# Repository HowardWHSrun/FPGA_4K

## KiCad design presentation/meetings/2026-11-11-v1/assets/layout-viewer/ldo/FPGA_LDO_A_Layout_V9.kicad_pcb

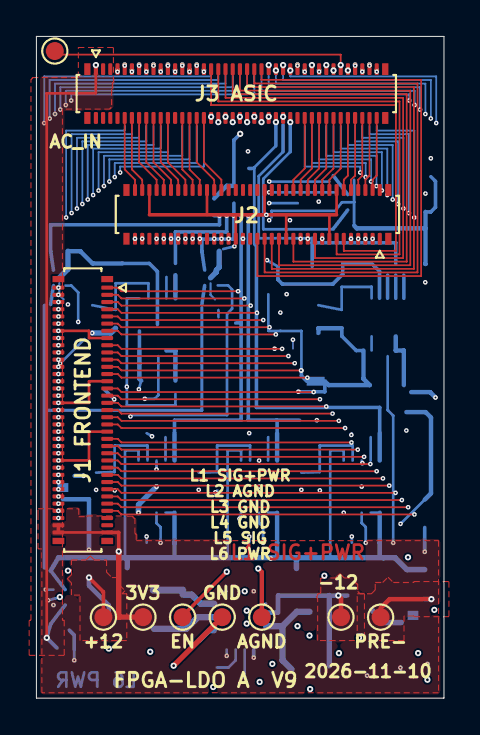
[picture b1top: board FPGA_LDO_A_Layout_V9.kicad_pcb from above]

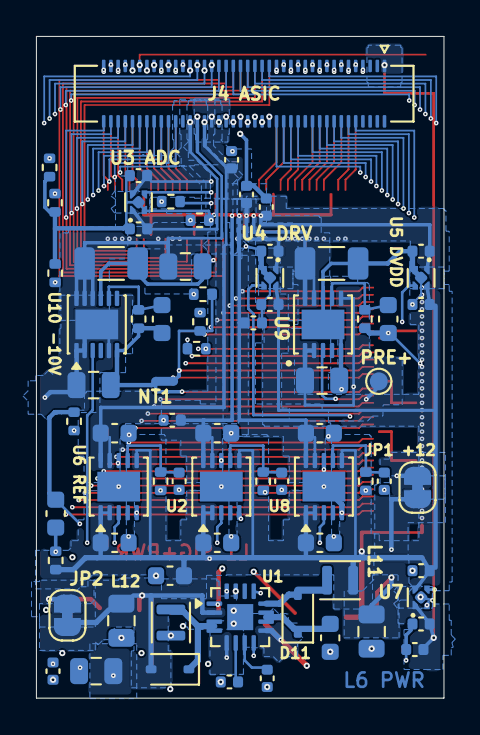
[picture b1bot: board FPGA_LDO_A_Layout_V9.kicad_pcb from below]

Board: 6 copper layers, 22.6 x 36.8 mm, 84 parts (73 on the bottom side), 136 nets.

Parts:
C1, C14, C21: 22uF; C_0805_2012Metric
C2: 100nF; C_0402_1005Metric
C3, C11: 4.7uF; C_0603_1608Metric
C15, C903, C1003: 1uF; C_0603_1608Metric
C16, C17: 10nF; C_0402_1005Metric
C51, C53, C54, C55, C56, C57, C203, C301, C302, C401, C402, C501, C502, C603, C701, C702, C803: 1uF; C_0402_1005Metric
C201, C202, C601, C602, C801, C802: 10uF; C_0603_1608Metric
C901, C1001, C1004: 10uF; C_0805_2012Metric
C902, C1002: 22uF; C_1206_3216Metric
D11, D12: B0540WS-7; D_SOD-323
J1, J2: DF40C-70DP-0.4V(51); Hirose_DF40C-70DP-0.4V_2x35-1MP_P0.4mm
J3: DF40C-80DP-0.4V(51); Hirose_DF40C-80DP-0.4V_2x40-1MP_P0.4mm
J4: DF40C-80DS-0.4V(51); Hirose_DF40C-80DS-0.4V_2x40_P0.4mm
JP1, JP2: Bridged; SolderJumper-2_P1.3mm_Bridged_RoundedPad1.0x1.5mm
L11, L12: 6.8uH; L_Murata_DFE201610P
NT1: NetTie_2; NetTie-2_SMD_Pad0.5mm
R1, R2, R3, R4, R5, R6, R16, R17, R18, R19: 10k; R_0402_1005Metric
R201, R601: 15k; R_0402_1005Metric
R801: 7.5k; R_0402_1005Metric
R901, R1001: 100k; R_0402_1005Metric
TP1: VIN_3V3; TestPoint_Pad_D1.0mm_Compact
TP2: STIM_POS_12V; TestPoint_Pad_D1.0mm_Compact
TP3: STIM_NEG_12V; TestPoint_Pad_D1.0mm_Compact
TP4: EN_ASIC_RAILS; TestPoint_Pad_D1.0mm_Compact
TP5: GND; TestPoint_Pad_D1.0mm_Compact
TP6: AGND; TestPoint_Pad_D1.0mm_Compact
TP7: ASIC_AC_IN; TestPoint_Pad_D1.0mm_Compact
TP8: STIM_PRE_POS; TestPoint_Pad_D1.0mm_Compact
TP9: STIM_PRE_NEG; TestPoint_Pad_D1.0mm_Compact
U1: LT3582EUD-12#PBF; QFN-16-1EP_3x3mm_P0.5mm_EP1.45x1.45mm
U2, U6, U8, U9: LT3042EDD#PBF; DFN-10-1EP_3x3mm_P0.5mm_EP1.65x2.38mm
U3, U4, U5, U7: TPS7A2015PDQNR; Texas_X2SON-4_1x1mm_P0.65mm
U10: LT3094EDD#PBF; DFN-12-1EP_3x3mm_P0.45mm_EP1.65x2.38mm

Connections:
/ASIC1_CLK32MHz_Out: J1.53, J4.45
/ASIC1_DATA1: J1.25, J4.79
/ASIC1_DATA2: J1.23, J4.77
/ASIC1_DATA3: J1.21, J4.75
/ASIC1_DATA4: J1.19, J4.73
/ASIC1_DATA5: J1.12, J4.43
/ASIC1_DATA6: J1.10, J4.41
/ASIC1_DATA7: J1.8, J4.39
/ASIC1_DATA8: J1.6, J4.37
/ASIC1_READ: J1.4, J4.35
/ASIC1_SYNC: J1.55, J4.47
/ASIC2_CLK32MHz_Out: J1.54, J4.19
/ASIC2_DATA1: J1.2, J4.33
/ASIC2_DATA2: J1.1, J4.31
/ASIC2_DATA3: J1.64, J4.29
/ASIC2_DATA4: J1.62, J4.27
/ASIC2_DATA5: J1.52, J4.17
/ASIC2_DATA6: J1.48, J4.15
/ASIC2_DATA7: J1.46, J4.13
/ASIC2_DATA8: J1.44, J4.11
/ASIC2_READ: J1.42, J4.9
/ASIC2_SYNC: J1.56, J4.21
/ASIC3_CLK32MHz_Out: J1.39, J4.70
/ASIC3_DATA1: J1.51, J4.80
/ASIC3_DATA2: J1.49, J4.78
/ASIC3_DATA3: J1.47, J4.76
/ASIC3_DATA4: J1.45, J4.74
/ASIC3_DATA5: J1.37, J4.68
/ASIC3_DATA6: J1.35, J4.66
/ASIC3_DATA7: J1.33, J4.64
/ASIC3_DATA8: J1.31, J4.62
/ASIC3_READ: J1.29, J4.60
/ASIC3_SYNC: J1.43, J4.72
/ASIC4_CLK32MHz_Out: J1.26, J4.20
/ASIC4_DATA1: J1.38, J4.32
/ASIC4_DATA2: J1.36, J4.30
/ASIC4_DATA3: J1.32, J4.28
/ASIC4_DATA4: J1.30, J4.26
/ASIC4_DATA5: J1.24, J4.18
/ASIC4_DATA6: J1.22, J4.16
/ASIC4_DATA7: J1.20, J4.14
/ASIC4_DATA8: J1.18, J4.12
/ASIC4_READ: J1.16, J4.10
/ASIC4_SYNC: J1.28, J4.22
/ASIC5_CLK32MHz_Out: J2.33, J3.45
/ASIC5_DATA1: J2.3, J3.79
/ASIC5_DATA2: J2.5, J3.77
/ASIC5_DATA3: J2.7, J3.75
/ASIC5_DATA4: J2.9, J3.73
/ASIC5_DATA5: J2.31, J3.43
/ASIC5_DATA6: J2.29, J3.41
/ASIC5_DATA7: J2.25, J3.39
/ASIC5_DATA8: J2.19, J3.37
/ASIC5_READ: J2.13, J3.35
/ASIC5_SYNC: J2.35, J3.47
/ASIC6_CLK32MHz_Out: J2.55, J3.19
/ASIC6_DATA1: J2.11, J3.33
/ASIC6_DATA2: J2.39, J3.31
/ASIC6_DATA3: J2.43, J3.29
/ASIC6_DATA4: J2.45, J3.27
/ASIC6_DATA5: J2.57, J3.17
/ASIC6_DATA6: J2.59, J3.15
/ASIC6_DATA7: J2.61, J3.13
/ASIC6_DATA8: J2.63, J3.11
/ASIC6_READ: J2.67, J3.9
/ASIC6_SYNC: J2.53, J3.21
/ASIC7_CLK32MHz_Out: J2.16, J3.70
/ASIC7_DATA1: J2.4, J3.80
/ASIC7_DATA2: J2.6, J3.78
/ASIC7_DATA3: J2.8, J3.76
/ASIC7_DATA4: J2.10, J3.74
/ASIC7_DATA5: J2.18, J3.68
/ASIC7_DATA6: J2.20, J3.66
/ASIC7_DATA7: J2.22, J3.64
/ASIC7_DATA8: J2.24, J3.62
/ASIC7_READ: J2.26, J3.60
/ASIC7_SYNC: J2.12, J3.72
/ASIC8_CLK32MHz_Out: J2.58, J3.20
/ASIC8_DATA1: J2.46, J3.32
/ASIC8_DATA2: J2.48, J3.30
/ASIC8_DATA3: J2.52, J3.28
/ASIC8_DATA4: J2.54, J3.26
/ASIC8_DATA5: J2.60, J3.18
/ASIC8_DATA6: J2.62, J3.16
/ASIC8_DATA7: J2.64, J3.14
/ASIC8_DATA8: J2.68, J3.12
/ASIC8_READ: J2.70, J3.10
/ASIC8_SYNC: J2.56, J3.22
/ASIC_AC_IN: J3.69, J4.69, R6.1, TP7.1
/ASIC_DVDD: C54.1, C502.1, J3.34, J4.34, R19.2, U5.1
/ASIC_REF_VCM: C57.1, C802.1, J3.40, J4.40, U8.9, U8.10
/ASIC_REF_VDD: C55.1, C602.1, J3.52, J4.52, U6.9, U6.10
/ASIC_VDD10: C902.1, J3.36, J4.36, U9.9, U9.10
/ASIC_VDD_ADC: C302.1, J3.56, J4.56, U3.1
/ASIC_VDD_CGEN: C56.1, C702.1, J3.1, J4.1, U7.1
/ASIC_VDD_DRIVER: C53.1, C402.1, J3.38, J4.38, U4.1
/ASIC_VDD_FE: C51.1, C202.1, J3.50, J4.50, U2.9, U2.10
/ASIC_VSS10: C1002.1, C1004.1, J3.54, J4.54, U10.10, U10.11, U10.12
/BOARD1_CLK: J1.40, J4.7
/BOARD1_SPI_CLK: J1.9, J4.63
/BOARD3_CLK: J2.69, J3.7
/BOARD3_SPI_CLK: J2.17, J3.63
/CAPP: C15.1, D11.1, U1.10, U1.11
/CHIP_RESET_SHARED: J1.17, J3.71, J4.71, R19.1
/EN_ASIC_RAILS: C3.1, R1.2, TP4.1, U1.8, U2.3, U3.3, U4.3, U5.3, U6.3, U7.3, U8.3, U9.3, U10.3
/FE_RESET_SHARED: J1.11, J3.65, J4.65, R16.1
/IMP_TST_SHARED: J1.13, J3.67, J4.67, R17.1
/RAMPN: C17.1, U1.6
/RAMPP: C16.1, U1.7
/SPI_LATCH_SHARED: J1.7, J3.61, J4.61, R18.1
/STIM_CHB_SHARED: J1.57, J3.49, J4.49, R4.1
/STIM_CHIP1_SPI_DL: J1.5, J4.59
/STIM_CHIP1_SPI_DR: J1.3, J4.57
/STIM_CHIP2_SPI_DL: J1.60, J4.25
/STIM_CHIP2_SPI_DR: J1.58, J4.23
/STIM_CHIP3_SPI_DL: J2.21, J3.59
/STIM_CHIP3_SPI_DR: J2.23, J3.57
/STIM_CHIP4_SPI_DL: J2.47, J3.25
/STIM_CHIP4_SPI_DR: J2.51, J3.23
/STIM_CLK_SHARED: J1.61, J3.53, J4.53, R5.1
/STIM_EN_SHARED: J1.59, J3.51, J4.51, R2.1
/STIM_NEG_12V: C21.1, D12.2, JP2.1, TP3.1, U1.2
/STIM_POS_12V: C14.1, JP1.1, TP2.1, U1.9
/STIM_PRE_NEG: C1001.1, JP2.2, TP9.1, U10.1, U10.2, U10.5, U10.13
/STIM_PRE_POS: C901.1, JP1.2, TP8.1, U9.1, U9.2, U9.6
/STIM_START_SHARED: J1.63, J3.55, J4.55, R3.1
/SW_N: D12.1, L12.1, U1.3, U1.4
/SW_P: D11.2, L11.2, U1.12
/VIN_3V3: C1.1, C2.1, C11.1, C201.1, C301.1, C401.1, C501.1, C601.1, C701.1, C801.1, J1.68, J1.69, J1.70, L11.1, R1.1, TP1.1, U1.5, U2.1, U2.2, U2.6, U3.4, U4.4, U5.4, U6.1, U6.2, U6.6, U7.4, U8.1, U8.2, U8.6
AGND: C51.2, C53.2, C54.2, C55.2, C56.2, C57.2, C201.2, C202.2, C203.2, C401.2, C402.2, C501.2, C502.2, C601.2, C602.2, C603.2, C701.2, C702.2, C801.2, C802.2, C803.2, C901.2, C902.2, C903.2, C1001.2, C1002.2, C1003.2, C1004.2, J3.42, J3.44, J4.42, J4.44, NT1.2, R6.2, R201.2, R601.2, R801.2, R901.2, R1001.2, TP6.1, U2.5, U2.8, U2.11, U4.2, U4.5, U5.2, U5.5, U6.5, U6.8, U6.11, U7.2, U7.5, U8.5, U8.8, U8.11, U9.5, U9.8, U9.11, U10.6, U10.9
GND: C1.2, C2.2, C3.2, C11.2, C14.2, C15.2, C16.2, C17.2, C21.2, C301.2, C302.2, J1.14, J1.15, J1.27, J1.34, J1.41, J1.50, J1.66, J2.14, J2.15, J2.27, J2.34, J2.41, J2.50, J2.66, J3.46, J3.48, J4.46, J4.48, L12.2, NT1.1, R2.2, R3.2, R4.2, R5.2, R16.2, R17.2, R18.2, TP5.1, U1.1, U1.13, U1.15, U1.16, U1.17, U3.2, U3.5
unnamed: C203.1, R201.1, U2.7
unnamed: C603.1, R601.1, U6.7
unnamed: C803.1, R801.1, U8.7
unnamed: C903.1, R901.1, U9.7
unnamed: C1003.1, R1001.1, U10.8

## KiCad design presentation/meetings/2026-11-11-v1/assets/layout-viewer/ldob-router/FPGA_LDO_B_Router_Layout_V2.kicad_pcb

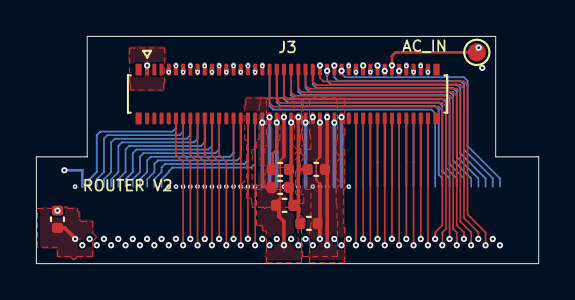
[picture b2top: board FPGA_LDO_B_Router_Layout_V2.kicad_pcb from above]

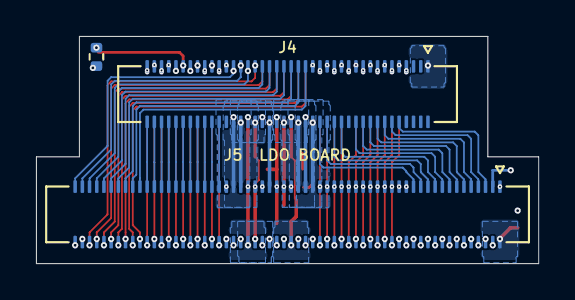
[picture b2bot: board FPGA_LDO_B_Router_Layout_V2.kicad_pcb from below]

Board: 6 copper layers, 27.9 x 12.6 mm, 11 parts (3 on the bottom side), 120 nets.

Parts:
C51, C53, C54, C55, C56, C57: 1uF; C_0402_1005Metric
J3: DF40C-80DP-0.4V(51); Hirose_DF40C-80DP-0.4V_2x40-1MP_P0.4mm
J4: DF40C-80DS-0.4V(51); Hirose_DF40C-80DS-0.4V_2x40_P0.4mm
J5: DF40C-120DS-0.4V(51); Hirose_DF40C-120DS-0.4V_2x60_P0.4mm
R6: 10k; R_0402_1005Metric
TP7: ASIC_AC_IN; TestPoint_Pad_D1.0mm_Compact

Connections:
/ASIC1_CLK32MHz_Out: J4.45, J5.111
/ASIC1_DATA1: J4.79, J5.77
/ASIC1_DATA2: J4.77, J5.76
/ASIC1_DATA3: J4.75, J5.74
/ASIC1_DATA4: J4.73, J5.71
/ASIC1_DATA5: J4.43, J5.109
/ASIC1_DATA6: J4.41, J5.107
/ASIC1_DATA7: J4.39, J5.105
/ASIC1_DATA8: J4.37, J5.103
/ASIC1_READ: J4.35, J5.101
/ASIC1_SYNC: J4.47, J5.113
/ASIC2_CLK32MHz_Out: J4.19, J5.39
/ASIC2_DATA1: J4.33, J5.1
/ASIC2_DATA2: J4.31, J5.51
/ASIC2_DATA3: J4.29, J5.49
/ASIC2_DATA4: J4.27, J5.47
/ASIC2_DATA5: J4.17, J5.37
/ASIC2_DATA6: J4.15, J5.35
/ASIC2_DATA7: J4.13, J5.33
/ASIC2_DATA8: J4.11, J5.31
/ASIC2_READ: J4.9, J5.29
/ASIC2_SYNC: J4.21, J5.41
/ASIC3_CLK32MHz_Out: J4.70, J5.89
/ASIC3_DATA1: J4.80, J5.99
/ASIC3_DATA2: J4.78, J5.97
/ASIC3_DATA3: J4.76, J5.95
/ASIC3_DATA4: J4.74, J5.93
/ASIC3_DATA5: J4.68, J5.87
/ASIC3_DATA6: J4.66, J5.85
/ASIC3_DATA7: J4.64, J5.83
/ASIC3_DATA8: J4.62, J5.81
/ASIC3_READ: J4.60, J5.79
/ASIC3_SYNC: J4.72, J5.91
/ASIC4_CLK32MHz_Out: J4.20, J5.15
/ASIC4_DATA1: J4.32, J5.25
/ASIC4_DATA2: J4.30, J5.23
/ASIC4_DATA3: J4.28, J5.21
/ASIC4_DATA4: J4.26, J5.19
/ASIC4_DATA5: J4.18, J5.13
/ASIC4_DATA6: J4.16, J5.11
/ASIC4_DATA7: J4.14, J5.9
/ASIC4_DATA8: J4.12, J5.7
/ASIC4_READ: J4.10, J5.5
/ASIC4_SYNC: J4.22, J5.17
/ASIC5_CLK32MHz_Out: J3.45, J5.112
/ASIC5_DATA1: J3.79, J5.120
/ASIC5_DATA2: J3.77, J5.118
/ASIC5_DATA3: J3.75, J5.78
/ASIC5_DATA4: J3.73, J5.68
/ASIC5_DATA5: J3.43, J5.110
/ASIC5_DATA6: J3.41, J5.108
/ASIC5_DATA7: J3.39, J5.106
/ASIC5_DATA8: J3.37, J5.104
/ASIC5_READ: J3.35, J5.102
/ASIC5_SYNC: J3.47, J5.114
/ASIC6_CLK32MHz_Out: J3.19, J5.16
/ASIC6_DATA1: J3.33, J5.30
/ASIC6_DATA2: J3.31, J5.28
/ASIC6_DATA3: J3.29, J5.26
/ASIC6_DATA4: J3.27, J5.24
/ASIC6_DATA5: J3.17, J5.14
/ASIC6_DATA6: J3.15, J5.12
/ASIC6_DATA7: J3.13, J5.10
/ASIC6_DATA8: J3.11, J5.8
/ASIC6_READ: J3.9, J5.6
/ASIC6_SYNC: J3.21, J5.18
/ASIC7_CLK32MHz_Out: J3.70, J5.90
/ASIC7_DATA1: J3.80, J5.100
/ASIC7_DATA2: J3.78, J5.98
/ASIC7_DATA3: J3.76, J5.96
/ASIC7_DATA4: J3.74, J5.94
/ASIC7_DATA5: J3.68, J5.88
/ASIC7_DATA6: J3.66, J5.86
/ASIC7_DATA7: J3.64, J5.84
/ASIC7_DATA8: J3.62, J5.82
/ASIC7_READ: J3.60, J5.80
/ASIC7_SYNC: J3.72, J5.92
/ASIC8_CLK32MHz_Out: J3.20, J5.42
/ASIC8_DATA1: J3.32, J5.52
/ASIC8_DATA2: J3.30, J5.50
/ASIC8_DATA3: J3.28, J5.48
/ASIC8_DATA4: J3.26, J5.46
/ASIC8_DATA5: J3.18, J5.40
/ASIC8_DATA6: J3.16, J5.38
/ASIC8_DATA7: J3.14, J5.36
/ASIC8_DATA8: J3.12, J5.34
/ASIC8_READ: J3.10, J5.32
/ASIC8_SYNC: J3.22, J5.44
/ASIC_AC_IN: J3.69, J4.69, R6.1, TP7.1
/ASIC_DVDD: C54.1, J3.34, J4.34, J5.53
/ASIC_REF_VCM: C57.1, J3.40, J4.40, J5.60
/ASIC_REF_VDD: C55.1, J3.52, J4.52, J5.72
/ASIC_VDD10: J3.36, J4.36, J5.55
/ASIC_VDD_ADC: J3.56, J4.56, J5.75
/ASIC_VDD_CGEN: C56.1, J3.1, J4.1, J5.2
/ASIC_VDD_DRIVER: C53.1, J3.38, J4.38, J5.57
/ASIC_VDD_FE: C51.1, J3.50, J4.50, J5.70
/ASIC_VSS10: J3.54, J4.54, J5.73
/BOARD1_CLK: J4.7, J5.27
/BOARD1_SPI_CLK: J4.63, J5.63
/BOARD3_CLK: J3.7, J5.4
/BOARD3_SPI_CLK: J3.63, J5.64
/CHIP_RESET_SHARED: J3.71, J4.71, J5.69
/FE_RESET_SHARED: J3.65, J4.65, J5.66
/IMP_TST_SHARED: J3.67, J4.67, J5.67
/SPI_LATCH_SHARED: J3.61, J4.61, J5.61
/STIM_CHB_SHARED: J3.49, J4.49, J5.116
/STIM_CHIP1_SPI_DL: J4.59, J5.59
/STIM_CHIP1_SPI_DR: J4.57, J5.58
/STIM_CHIP2_SPI_DL: J4.25, J5.45
/STIM_CHIP2_SPI_DR: J4.23, J5.43
/STIM_CHIP3_SPI_DL: J3.59, J5.56
/STIM_CHIP3_SPI_DR: J3.57, J5.54
/STIM_CHIP4_SPI_DL: J3.25, J5.22
/STIM_CHIP4_SPI_DR: J3.23, J5.20
/STIM_CLK_SHARED: J3.53, J4.53, J5.117
/STIM_EN_SHARED: J3.51, J4.51, J5.115
/STIM_START_SHARED: J3.55, J4.55, J5.119
AGND: C51.2, C53.2, C54.2, C55.2, C56.2, C57.2, J3.42, J3.44, J4.42, J4.44, J5.62, R6.2
GND: J3.46, J3.48, J4.46, J4.48, J5.3, J5.65

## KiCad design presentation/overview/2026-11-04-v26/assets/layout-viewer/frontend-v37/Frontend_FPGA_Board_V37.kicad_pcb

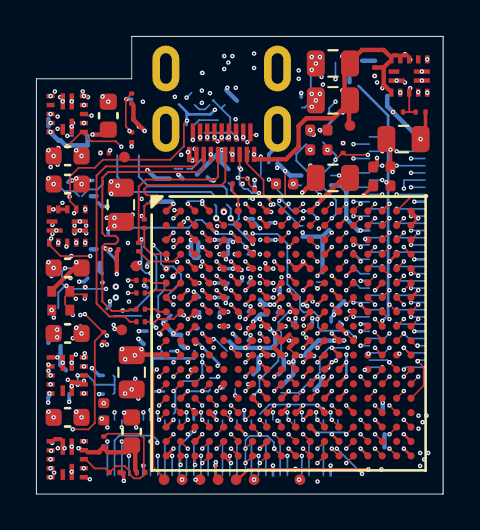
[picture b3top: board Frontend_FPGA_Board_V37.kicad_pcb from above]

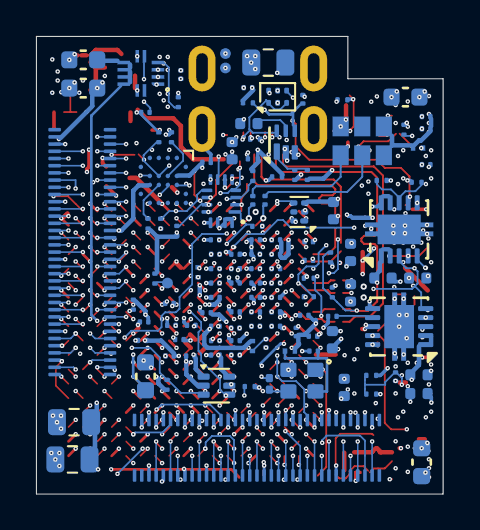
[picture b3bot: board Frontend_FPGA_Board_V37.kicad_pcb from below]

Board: 10 copper layers, 22.6 x 25.4 mm, 185 parts (125 on the bottom side), 190 nets.

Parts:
C1, C2, C12, C13, C21, C22, C85, C86: 22uF; C_0603_1608Metric
C3, C14, C23, C87: 22pF; C_0201_GRM03_Murata_0p22Gap
C4, C10, C89: 100uF; C_0805_2012Metric
C5, C6, C25, C36, C37, C51, C54, C96, C107: 4.7uF; C_0201_GRM03_Murata_0p22Gap
C7, C8, C9, C11, C18, C19, C20, C26, C27, C28, C29, C32, C33, C34, C35, C38, C39, C40, C52, C53, C55, C56, C57, C58, C80, C91, C92, C93, C97, C98, C99, C100: 470nF; C_0201_GRM03_Murata_0p22Gap
C15, C42, C59: 47uF; C_0805_2012Metric
C16, C17, C24, C30, C31, C43, C44, C45, C47, C48, C49, C90, C94, C95, C101: 4.7uF; C_0402_1005Metric
C46, C50: 10nF; C_0201_GRM03_Murata_0p22Gap
C60, C63, C78, C79, C81, C82, C83, C88, C105, C106, C200, C201, C202, C203, C204, C205, C209: 100nF; C_0201_GRM03_Murata_0p22Gap
C61, C84: 1uF; C_0402_1005Metric
C62: 220nF; C_0201_GRM03_Murata_0p22Gap
C75, C76, C102, C104: 22uF / 6.3V; C_0603_1608Metric
C77: 22nF / 16V; C_0201_GRM03_Murata_0p22Gap
C103: 470nF / 6.3V; C_0201_GRM03_Murata_0p22Gap
C206, C207, C208: 22uF / 10V; C_0805_2012Metric
J1, J2: DF40C-70DS-0.4V(51); Hirose_DF40C-70DS-0.4V_2x35_P0.4mm
J3: Micro-HDMI 467651001; Molex_MicroHDMI_46765_1xxx
L1, L2, L3, L4: MPZ0603S121HT000; TDK_MPZ0603S121HT000_0201_Land_0p25x0p30_Gap0p30
R1, R4, R5, R41, R55, R59: 200k; R_0201_ERA1A_Panasonic_0p30Gap
R2: 301k; R_0201_ERA1A_Panasonic_0p30Gap
R3, R9, R11, R14, R17, R18, R19, R22, R38, R43, R58: 4.99k; R_0201_ERA1A_Panasonic_0p30Gap
R7: 150k; R_0402_TE_CPF_Reflow_0p50Gap
R8: 100k; R_0402_TE_CPF_Reflow_0p50Gap
R10: 1.3k; R_0201_ERA1A_Panasonic_0p30Gap
R13: 2.49k; R_0201_ERA1A_Panasonic_0p30Gap
R16: 100R; R_0201_ERA1A_Panasonic_0p30Gap
R20, R21, R49, R50: 4.7k; R_0201_ERA1A_Panasonic_0p30Gap
R25: 470R; R_0201_ERA1A_Panasonic_0p30Gap
R27: 1k; R_0201_ERA1A_Panasonic_0p30Gap
R37: 24k / 1%; R_0201_ERA1A_Panasonic_0p30Gap
R42: 150k; R_0201_ERA1A_Panasonic_0p30Gap
R44: 33R; R_0201_0603Metric
R45: 4.64k; R_0201_ERA1A_Panasonic_0p30Gap
R46, R47, R48, R57: 10k; R_0201_ERA1A_Panasonic_0p30Gap
R51, R52, R53: 47k; R_0201_ERA1A_Panasonic_0p30Gap
R54: 22k; R_0201_ERA1A_Panasonic_0p30Gap
R60: 44.2k; R_0201_ERA1A_Panasonic_0p30Gap
TP1, TP2, TP3, TP4, TP5, TP6, TP7, TP8, TP9, TP10, TP11, TP12, TP13, TP14: 0.6mm COPPER; TestPoint_Pad_D0.6mm_Edge_NoPaste
U1: XC7A35T-2CSG325I; Xilinx_CSG325
U2, U3, U4, U13, U16: MPM3834CGPA; MPM3834C_ECLGA14_2.5x2.5mm
U5, U6: TPS74801DRCRM3; VSON-10-1EP_3x3mm_P0.5mm_EP1.65x2.4mm
U7: W25Q128JWYIQ; Winbond_WLCSP-21_P0.5mm
U8: SN74AVC4T774RSVR / SPI x1; TI_RSV_UQFN16_1.8x2.6mm_P0.4mm
U10: MP5077GG-Z; MPS_MP5077_QFN12_2x2mm_P0.4mm
U11: 74AUP2G07GM / dual reset OD; Nexperia_SOT886_XSON6_1x1.45mm
U12: TPS389001 / timed rail-ready reset; TI_DSE0006A_WSON6_1p5x1p5_P0p5_Manufacturer
U14: SN74AUP1G14 / SPI OE; Texas_USON-6_1x1.45mm_P0.5mm_SMD
U15: SN74AXC1T45DRLR; SOT-563
Y1: AX3DAF1-125.0000T3 / 125 MHz; Abracon_AX3_3225_6pin
Y2: SiT1615A / 25 MHz / 1.5 V; SiTime_2016_4pin

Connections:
1V4_GTP_IN: C43.2, C47.2, C86.1, C87.1, R41.1, U5.1 (IN), U5.2 (IN), U6.1 (IN), U6.2 (IN), U13.6 (OUT_S), U13.9 (OUT), U13.10 (OUT)
/ASIC1_CLK32MHz_Out: J1.11, U1.P15 (L11P_T1_SRCC)
/ASIC1_DATA1: J1.3, U1.M16 (L7P_T1_D09)
/ASIC1_DATA2: J1.4, U1.N18 (L10P_T1_D14)
/ASIC1_DATA3: J1.5, U1.M17 (L7N_T1_D10)
/ASIC1_DATA4: J1.6, U1.P18 (L10N_T1_D15)
/ASIC1_DATA5: J1.7, U1.N16 (L9P_T1_DQS)
/ASIC1_DATA6: J1.8, U1.L18 (L4N_T0_D05)
/ASIC1_DATA7: J1.9, U1.K15 (L5N_T0_D07)
/ASIC1_DATA8: J1.10, U1.K18 (L3N_T0_DQS_EMCCLK)
/ASIC1_READ: J1.12, U1.K17 (L4P_T0_D04)
/ASIC1_SYNC: J1.13, U1.J15 (L2P_T0_D02)
/ASIC2_CLK32MHz_Out: J1.23, U1.E16 (L14P_T2_SRCC)
/ASIC2_DATA1: J1.18, U1.H18 (L23N_T3_FWE_B)
/ASIC2_DATA2: J1.21, U1.G14 (L22P_T3_A17)
/ASIC2_DATA3: J1.16, U1.H16 (L20P_T3_A20)
/ASIC2_DATA4: J1.17, U1.H14 (IO25)
/ASIC2_DATA5: J1.20, U1.H17 (L23P_T3_FOE_B)
/ASIC2_DATA6: J1.24, U1.G16 (L20N_T3_A19)
/ASIC2_DATA7: J1.22, U1.G17 (L19P_T3_A22)
/ASIC2_DATA8: J1.19, U1.G15 (L21P_T3_DQS)
/ASIC2_READ: J1.25, U1.F14 (L22N_T3_A16)
/ASIC2_SYNC: J1.26, U1.F18 (L19N_T3_A21_VREF)
/ASIC3_CLK32MHz_Out: J1.36, U1.E15 (L13P_T2_MRCC)
/ASIC3_DATA1: J1.31, U1.F15 (L21N_T3_DQS_A18)
/ASIC3_DATA2: J1.28, U1.F17 (L24P_T3_RS1)
/ASIC3_DATA3: J1.35, U1.D14 (L12N_T1_MRCC)
/ASIC3_DATA4: J1.30, U1.E18 (L24N_T3_RS0)
/ASIC3_DATA5: J1.29, U1.E13 (L12P_T1_MRCC)
/ASIC3_DATA6: J1.32, U1.E17 (L17P_T2_A26)
/ASIC3_DATA7: J1.39, U1.D15 (L13N_T2_MRCC)
/ASIC3_DATA8: J1.33, U1.D11 (L6P_T0)
/ASIC3_READ: J1.37, U1.C11 (L4P_T0)
/ASIC3_SYNC: J1.38, U1.D18 (L17N_T2_A25)
/ASIC4_CLK32MHz_Out: J1.43, U1.D13 (L11P_T1_SRCC)
/ASIC4_DATA1: J1.44, U1.C14 (L9P_T1_DQS_AD3P)
/ASIC4_DATA2: J1.40, U1.D16 (L14N_T2_SRCC)
/ASIC4_DATA3: J1.47, U1.C13 (L11N_T1_SRCC)
/ASIC4_DATA4: J1.45, U1.C9 (L2N_T0_AD8N)
/ASIC4_DATA5: J1.49, U1.C12 (L6N_T0_VREF)
/ASIC4_DATA6: J1.42, U1.C16 (L16P_T2_A28)
/ASIC4_DATA7: J1.53, U1.B12 (L7P_T1_AD2P)
/ASIC4_DATA8: J1.46, U1.B16 (L15P_T2_DQS)
/ASIC4_READ: J1.48, U1.B15 (L9N_T1_DQS_AD3N)
/ASIC4_SYNC: J1.51, U1.A13 (L8P_T1_AD10P)
/ASIC5_CLK32MHz_Out: J2.7, U1.R2 (L13P_T2_MRCC)
/ASIC5_DATA1: J2.11, U1.N2 (L11N_T1_SRCC)
/ASIC5_DATA2: J2.6, U1.U1 (L15N_T2_DQS)
/ASIC5_DATA3: J2.4, U1.P1 (L9N_T1_DQS)
/ASIC5_DATA4: J2.3, U1.N1 (L9P_T1_DQS)
/ASIC5_DATA5: J2.5, U1.K1 (L3N_T0_DQS)
/ASIC5_DATA6: J2.12, U1.U6 (L20P_T3)
/ASIC5_DATA7: J2.13, U1.L2 (L4N_T0)
/ASIC5_DATA8: J2.10, U1.U2 (L15P_T2_DQS)
/ASIC5_READ: J2.8, U1.T2 (L14N_T2_SRCC)
/ASIC5_SYNC: J2.9, U1.M1 (L7N_T1)
/ASIC6_CLK32MHz_Out: J2.20, U1.R3 (L14P_T2_SRCC)
/ASIC6_DATA1: J2.16, U1.R1 (L13N_T2_MRCC)
/ASIC6_DATA2: J2.19, U1.M2 (L7P_T1)
/ASIC6_DATA3: J2.24, U1.T4 (L17P_T2)
/ASIC6_DATA4: J2.17, U1.K2 (L3P_T0_DQS)
/ASIC6_DATA5: J2.18, U1.T3 (L17N_T2)
/ASIC6_DATA6: J2.25, U1.L3 (L5N_T0)
/ASIC6_DATA7: J2.22, U1.U4 (L18P_T2)
/ASIC6_DATA8: J2.23, U1.P3 (L12N_T1_MRCC)
/ASIC6_READ: J2.21, U1.K3 (L4P_T0)
/ASIC6_SYNC: J2.26, U1.V6 (L23N_T3)
/ASIC7_CLK32MHz_Out: J2.31, U1.P4 (L12P_T1_MRCC)
/ASIC7_DATA1: J2.33, U1.N4 (L10N_T1)
/ASIC7_DATA2: J2.30, U1.V4 (L18N_T2)
/ASIC7_DATA3: J2.29, U1.M4 (L10P_T1)
/ASIC7_DATA4: J2.36, U1.U7 (L23P_T3)
/ASIC7_DATA5: J2.28, U1.T5 (L21N_T3_DQS)
/ASIC7_DATA6: J2.32, U1.U5 (L20N_T3)
/ASIC7_DATA7: J2.35, U1.R5 (L21P_T3_DQS)
/ASIC7_DATA8: J2.37, U1.R6 (IO25)
/ASIC7_READ: J2.39, U1.R7 (L22P_T3)
/ASIC7_SYNC: J2.38, U1.V7 (L24N_T3)
/ASIC8_CLK32MHz_Out: J2.49, U1.R16 (L14P_T2_SRCC)
/ASIC8_DATA1: J2.53, U1.R17 (L14N_T2_SRCC)
/ASIC8_DATA2: J2.46, U1.V12 (L21P_T3_DQS)
/ASIC8_DATA3: J2.40, U1.U9 (L24P_T3_A01_D17)
/ASIC8_DATA4: J2.48, U1.U12 (L22N_T3_A04_D20)
/ASIC8_DATA5: J2.47, U1.T13 (L19N_T3_A09_D25_VREF)
/ASIC8_DATA6: J2.43, U1.U11 (L23P_T3_A03_D19)
/ASIC8_DATA7: J2.45, U1.T12 (L22P_T3_A05_D21)
/ASIC8_DATA8: J2.44, U1.V11 (L23N_T3_A02_D18)
/ASIC8_READ: J2.42, U1.V9 (L24N_T3_A00_D16)
/ASIC8_SYNC: J2.51, U1.T17 (L16P_T2_CSI_B)
/CLK25_RAW: R44.1, Y2.3 (OUT)
/CLK25_VDD: C88.1, L3.2, Y2.4 (VDD)
/FB_GTP_1V4: C87.2, R41.2, R42.1, U13.5 (FB)
/FB_VIN_3V3: R59.2, R60.1, U16.5 (FB)
/FE_RESET_SHARED: J1.64, U1.A15 (L10N_T1_AD11N)
/GPIO_CMD_N: J3.14 (GPIO_CMD_N), U1.V2 (L16N_T2)
/GPIO_CMD_P: J3.12 (GPIO_CMD_P), U1.V3 (L16P_T2)
/IMP_TST_SHARED: J1.63, U1.A12 (L7N_T1_AD2N)
/NONSTIM_BOARD1_SPI_DL: J1.58, U1.B17 (L16N_T2_A27)
/NONSTIM_BOARD1_SPI_DR: J1.59, U1.B11 (L4N_T0)
/NONSTIM_BOARD2_SPI_DL: J2.63, U1.U16 (L17N_T2_A13_D29)
/NONSTIM_BOARD2_SPI_DR: J2.59, U1.T14 (L13P_T2_MRCC)
/STIM_CHIP1_SPI_DL: J1.65, U1.A9 (L3N_T0_DQS_AD1N)
/STIM_CHIP1_SPI_DR: J1.60, U1.B14 (L10P_T1_AD11P)
/STIM_CHIP2_SPI_DL: J1.62, U1.A17 (L15N_T2_DQS_ADV_B)
/STIM_CHIP3_SPI_DL: J2.56, U1.V13 (L21N_T3_DQS_A06_D22)
/STIM_CHIP4_SPI_DR: J2.61, U1.T15 (L13N_T2_MRCC)
BOARD1_CLK: J1.56, U1.C17 (L18P_T2_A24)
BOARD1_SPI_CLK: J1.54, U1.C18 (L18N_T2_A23)
BOARD2_CLK: J1.61, U1.A10 (L5N_T0_AD9N)
BOARD2_SPI_CLK: J1.55, U1.B10 (L5P_T0_AD9P)
BOARD3_CLK: J2.54, U1.V8 (L24P_T3)
BOARD3_SPI_CLK: J2.55, U1.U10 (IO25)
BOARD4_CLK: J2.52, U1.T7 (L22N_T3)
BOARD4_SPI_CLK: J2.65, U1.T18 (L15N_T2_DQS_DOUT_CSO_B)
BOOT_RAILS_PG_3V3: R9.2, TP10.1 (PAD_1), U4.11 (PG), U5.3 (PG), U6.5 (EN), U12.3 (MR_PG)
BOOT_RESET_N: R47.2, U11.1 (1A_RESET_N), U11.3 (2A_RESET_N), U12.6 (RESET_N_OD), U14.2
CABLE_TARGET_SENSE: J3.1 (SENSE), R27.2
CHIP_RESET_SHARED: J1.52, U1.J16 (L2N_T0_D03)
CLK25_PL: R44.2, U1.N3 (L11P_T1_SRCC)
EN_GTPWR_1V5: R58.2, U1.M15 (L6N_T0_D08_VREF), U15.3
EN_GTPWR_3V3: R57.1, U13.3 (EN), U15.4
FLASH_CS_N_1V8: R22.2, U7.1, U8.11 (B2_CS)
FLASH_DQ0_1V8: R53.2, U7.5, U8.10 (B3_MOSI)
FLASH_DQ1_1V8: R51.1, U7.2, U8.9 (B4_MISO)
FLASH_HOLD_N_1V8: R21.2, U7.7
FLASH_READY_SENSE: R45.2, R46.1, U12.1 (SENSE_DIV)
FLASH_SCK_1V8: R52.1, U7.6, U8.12 (B1_SCK)
FLASH_TRANSLATOR_OE_N: R48.2, U8.7 (OE_N), U14.4
FLASH_WP_N_1V8: R20.2, U7.3
FPGA_DONE: R38.2, TP12.1 (PAD_1), U1.F12 (DONE_0)
FPGA_INIT_B: R18.2, TP11.1 (PAD_1), U1.T10 (INIT_B_0), U11.4 (2Y_INIT_OD)
FPGA_JTAG_TCK: J3.17 (TCK), U1.F8 (TCK_0)
FPGA_JTAG_TDI: J3.15 (TDI), U1.T9 (TDI_0)
FPGA_JTAG_TDO: J3.18 (TDO), U1.T8 (TDO_0)
FPGA_JTAG_TMS: J3.2 (TMS), U1.R8 (TMS_0)
FPGA_PROGRAM_B: R17.2, U1.P10 (PROGRAM_B_0), U11.6 (1Y_PROGRAM_OD)
FPGA_PUDC_B: R25.2, U1.J18 (L3P_T0_DQS_PUDC_B)
FPGA_QSPI_CCLK: R49.2, U1.E8 (CCLK_0), U8.1 (A1_CCLK)
FPGA_QSPI_CS_N: R19.2, U1.L15 (L6P_T0_FCS_B), U8.2 (A2_CS)
FPGA_QSPI_DQ0: R50.2, U1.K16 (L1P_T0_D00_MOSI), U8.3 (A3_MOSI)
FPGA_QSPI_DQ1: R54.1, U1.L17 (L1N_T0_D01_DIN), U8.4 (A4_MISO)
GND: C1.2, C2.2, C4.2, C5.2, C6.2, C7.2, C8.2, C9.2, C10.2, C11.2, C12.2, C13.2, C15.2, C16.2, C17.2, C18.2, C19.2, C20.2, C21.2, C22.2, C24.2, C25.2, C26.2, C27.2, C28.2, C29.2, C30.2, C31.2, C32.2, C33.2, C34.2, C35.2, C36.2, C37.2, C38.2, C39.2, C40.2, C42.2, C43.1, C44.2, C45.2, C46.2, C47.1, C48.2, C49.2, C50.2, C51.2, C52.2, C53.2, C54.2, C55.2, C56.2, C58.2, C59.2, C60.2, C61.2, C62.2, C63.2, C75.2, C76.2, C77.2, C80.2, C81.2, C82.2, C83.2, C84.2, C85.2, C86.2, C88.2, C89.2, C90.2, C91.2, C92.2, C93.2, C94.2, C95.2, C96.2, C97.2, C98.2, C99.2, C100.2, C101.2, C102.2, C103.2, C104.2, C105.2, C106.2, C107.2, C206.2, C207.2, C208.2, C209.2, J1.14, J1.15, J1.27, J1.34, J1.41, J1.50, J1.66, J2.14, J2.15, J2.27, J2.34, J2.41, J2.50, J2.66, J3.4 (GND), J3.7 (GND), J3.10 (GND), J3.13 (GND), J3.16 (GND), J3.SH (SHIELD), L2.1, R2.2, R5.2, R8.2, R11.2, R14.2, R37.2, R42.2, R46.2, R51.2, R52.2, R54.2, R55.2, R57.2, R60.2, TP1.1 (PAD_1), TP13.1 (PAD_1), U1.A1 (GND_[75_balls]), U1.A3 (MGTPRXN1_216), U1.A4 (MGTPRXP1_216), U1.A5 (GND), U1.A7 (GND), U1.A8 (GND), U1.A11 (GND), U1.A18 (GND), U1.B3 (GND), U1.B7 (GND), U1.B8 (GND), U1.B18 (GND), U1.C2 (GND), U1.C3 (MGTPRXN2_216), U1.C4 (MGTPRXP2_216), U1.C6 (GND), U1.C7 (GND), U1.C15 (GND), U1.D3 (GND), U1.D4 (GND), U1.D7 (GND), U1.D12 (GND), U1.E2 (GND), U1.E3 (MGTPRXN0_216), U1.E4 (MGTPRXP0_216), U1.E6 (GND), U1.E7 (GND), U1.E9 (GND), U1.E12 (CFGBVS_0), U1.F4 (GND), U1.F6 (GND), U1.F10 (GND), U1.F13 (M2_0), U1.F16 (GND), U1.G1 (GND), U1.G3 (MGTPRXN3_216), U1.G4 (MGTPRXP3_216), U1.G5 (GND), U1.G6 (GND), U1.G7 (GND), U1.G9 (GND), U1.G11 (GND), U1.G13 (GND), U1.H3 (GND), U1.H4 (GND), U1.H5 (GND), U1.H6 (GND), U1.H8 (GND), U1.H10 (GND), U1.H12 (GND), U1.J1 (GND), U1.J2 (GND), U1.J3 (GND), U1.J7 (GND), U1.J11 (GND), U1.J13 (GND), U1.J17 (GND), U1.K4 (GND), U1.K8 (GND), U1.K12 (GND), U1.K14 (GND), U1.L1 (GND), U1.L7 (GND), U1.L11 (GND), U1.L13 (GND), U1.M8 (GND), U1.M9 (DXN_0), U1.M10 (DXP_0), U1.M12 (GND), U1.M18 (GND), U1.N5 (GND), U1.N7 (GND), U1.N9 (GND), U1.N11 (GND), U1.N13 (GND), U1.N15 (GND), U1.P2 (GND), U1.P8 (GND), U1.P12 (GND), U1.R9 (GND), U1.R11 (M1_0), U1.T6 (GND), U1.T16 (GND), U1.U3 (GND), U1.U13 (GND), U1.V1 (GND), U1.V10 (GND), U1.V18 (GND), U2.2 (PGND), U2.4 (AGND), U2.7 (PGND), U2.8 (PGND), U3.2 (PGND), U3.4 (AGND), U3.7 (PGND), U3.8 (PGND), U4.2 (PGND), U4.4 (AGND), U4.7 (PGND), U4.8 (PGND), U5.6 (GND), U5.11 (GND_EP), U6.6 (GND), U6.11 (GND_EP), U7.4, U8.6 (DIR4_L), U8.8 (GND), U10.2 (GND), U11.2 (GND), U12.2 (GND), U13.2 (PGND), U13.4 (AGND), U13.7 (PGND), U13.8 (PGND), U14.3, U15.2, U16.2 (PGND), U16.4 (AGND), U16.7 (PGND), U16.8 (PGND), Y1.3 (GND), Y2.2 (GND)
GNDADC_XADC: C57.2, L2.2, U1.J9 (GNDADC_0), U1.K9 (VREFN_0), U1.K10 (VP_0), U1.L9 (VN_0), U1.L10 (VREFP_0)
GTP_REFCLK1_N: C79.2, U1.B5 (MGTREFCLK1N_216)
GTP_REFCLK1_P: C78.2, U1.B6 (MGTREFCLK1P_216)
GTP_TX0_N: C201.1, J3.5 (TX0_REC_N)
GTP_TX0_P: C200.1, J3.3 (TX0_REC_P)
MGTAVCC_1V0: C45.1, C51.1, C52.1, C53.1, R10.1, TP7.1 (PAD_1), U1.B4 (MGTAVCC), U1.C5 (MGTAVCC), U1.E5 (MGTAVCC), U1.F5 (MGTAVCC), U5.9 (OUT), U5.10 (OUT)
MGTAVTT_1V2: C49.1, C54.1, C55.1, C56.1, R13.1, R16.1, TP8.1 (PAD_1), U1.A2 (MGTAVTT), U1.C1 (MGTAVTT), U1.E1 (MGTAVTT), U1.F3 (MGTAVTT), U1.G2 (MGTAVTT), U6.9 (OUT), U6.10 (OUT)
unnamed: C203.1, J3.8 (TX1_REC_N)
unnamed: C202.1, J3.6 (TX1_REC_P)
unnamed: C205.1, J3.11 (TX2_REC_N)
unnamed: C204.1, J3.9 (TX2_REC_P)
unnamed: C201.2, U1.H1 (MGTPTXN0_216)
unnamed: C203.2, U1.F1 (MGTPTXN1_216)
unnamed: C205.2, U1.D1 (MGTPTXN2_216)
unnamed: C200.2, U1.H2 (MGTPTXP0_216)
unnamed: C202.2, U1.F2 (MGTPTXP1_216)
unnamed: C204.2, U1.D2 (MGTPTXP2_216)
unnamed: R16.2, U1.A6 (MGTRREF_216)
unnamed: C3.2, R1.2, R2.1, U2.5 (FB)
unnamed: C14.2, R4.2, R5.1, R55.1, U3.5 (FB)
unnamed: C23.2, R7.2, R8.1, U4.5 (FB)
unnamed: R10.2, R11.1, U5.8 (FB)
unnamed: C46.1, U5.7 (SS)
unnamed: R13.2, R14.1, U6.8 (FB)
unnamed: C50.1, U6.7 (SS)
unnamed: R37.1, U10.4 (ILIM)
unnamed: C77.1, U10.5 (SS)
unnamed: C84.1, U12.5 (CT)
OSC125_3V3: C80.1, C81.1, L4.2, Y1.1 (OE), Y1.6 (VDD)
OSC125_N: C79.1, Y1.5 (OUTN)
OSC125_P: C78.1, Y1.4 (OUTP)
PG_CORE_1V0: R3.2, U2.11 (PG), U3.3 (EN), U4.3 (EN), U10.1 (EN)
PG_GTP_1V4: R43.2, U5.5 (EN), U13.11 (PG)
SPI_LATCH_SHARED: J1.67, U1.A14 (L8N_T1_AD10N)
STIM_CHB_SHARED: J2.64, U1.U15 (L17P_T2_A14_D30)
STIM_CHIP2_SPI_DR: J1.57, U1.B9 (L3P_T0_DQS_AD1P)
STIM_CHIP3_SPI_DR: J2.57, U1.R13 (L19P_T3_A10_D26)
STIM_CHIP4_SPI_DL: J2.62, U1.V16 (L18P_T2_A12_D28)
STIM_CLK_SHARED: J2.67, U1.V17 (L18N_T2_A11_D27)
STIM_EN_SHARED: J2.58, U1.V14 (L20N_T3_A07_D23)
STIM_START_SHARED: J2.60, U1.U14 (L20P_T3_A08_D24)
SWITCHED_3V3: C76.1, C104.1, C106.1, L4.1, TP3.1 (PAD_1), U10.7 (VOUT), U10.8 (VOUT), U10.9 (VOUT), U10.10 (VOUT), U15.6
VCCADC_1V8: C57.1, L1.2, U1.J10 (VCCADC_0)
VCCAUX_1V8: C13.1, C14.1, C15.1, C16.1, C17.1, C18.1, C19.1, C20.1, C58.1, C59.1, C60.1, C62.1, C94.1, C95.1, C96.1, C97.1, C98.1, C99.1, C100.1, L1.1, R4.1, R17.1, R18.1, R20.1, R21.1, R22.1, R27.1, R38.1, R45.1, R49.1, R53.1, TP5.1 (PAD_1), TP9.1 (PAD_1), U1.E10 (VCCO_0), U1.E11 (VCCBATT_0), U1.G12 (VCCAUX_[5_balls]), U1.H13 (VCCAUX), U1.K13 (VCCAUX), U1.M13 (VCCAUX), U1.P13 (VCCAUX), U1.R10 (VCCO_0), U1.R12 (M0_0), U3.6 (OUT_S), U3.9 (OUT), U3.10 (OUT), U7.8, U8.13 (VCCB_1V8)
VCCINT_1V0: C2.1, C3.1, C4.1, C5.1, C6.1, C7.1, C8.1, C9.1, C10.1, C11.1, C89.1, C90.1, C91.1, C92.1, C93.1, R1.1, TP4.1 (PAD_1), U1.F7 (VCCINT_1V0), U1.F9 (VCCINT_1V0), U1.F11 (VCCBRAM/VCCINT_[21_balls]), U1.G8 (VCCINT_1V0), U1.G10 (VCCBRAM_1V0), U1.H7 (VCCINT_1V0), U1.H9 (VCCINT_1V0), U1.H11 (VCCBRAM_1V0), U1.J8 (VCCINT_1V0), U1.J12 (VCCINT_1V0), U1.K7 (VCCINT_1V0), U1.K11 (VCCINT_1V0), U1.L8 (VCCINT_1V0), U1.L12 (VCCINT_1V0), U1.M7 (VCCINT_1V0), U1.M11 (VCCINT_1V0), U1.N8 (VCCINT_1V0), U1.N10 (VCCINT_1V0), U1.N12 (VCCINT_1V0), U1.P9 (VCCINT_1V0), U1.P11 (VCCINT_1V0), U2.6 (OUT_S), U2.9 (OUT), U2.10 (OUT)
VCCO_1V5: C22.1, C23.1, C24.1, C25.1, C26.1, C27.1, C28.1, C29.1, C30.1, C31.1, C32.1, C33.1, C34.1, C35.1, C36.1, C37.1, C38.1, C39.1, C40.1, C42.1, C61.1, C63.1, C101.1, C105.1, C107.1, L3.1, R7.1, R19.1, R25.1, R48.1, R50.1, R58.1, TP6.1 (PAD_1), U1.A16 (VCCO), U1.B13 (VCCO), U1.C10 (VCCO), U1.D17 (VCCO), U1.E14 (VCCO), U1.G18 (VCCO), U1.H15 (VCCO), U1.L6 (VCCO), U1.L16 (VCCO), U1.M3 (VCCO), U1.P7 (VCCO), U1.P17 (VCCO), U1.R4 (VCCO), U1.R14 (VCCO), U1.T1 (VCCO), U1.T11 (VCCO), U1.U8 (VCCO), U1.U18 (VCCO), U1.V5 (VCCO), U1.V15 (VCCO), U4.6 (OUT_S), U4.9 (OUT), U4.10 (OUT), U8.5 (DIR3_H), U8.14 (VCCA_1V5), U8.15 (DIR1_H), U8.16 (DIR2_H), U14.6, U15.1, U15.5
VIN_3V3: C1.1, C12.1, C21.1, C44.1, C48.1, C75.1, C82.1, C83.1, C85.1, C102.1, C103.1, C208.1, J1.68, R3.1, R9.1, R43.1, R47.1, R59.1, TP2.1 (PAD_1), U2.3 (EN), U2.12 (IN), U2.13 (IN), U2.14 (IN), U3.12 (IN), U3.13 (IN), U3.14 (IN), U4.12 (IN), U4.13 (IN), U4.14 (IN), U5.4 (BIAS), U6.4 (BIAS), U10.3 (VCC), U10.6 (VIN), U10.11 (VIN), U11.5 (VCC_3V3), U12.4 (VDD_3V3), U13.12 (IN), U13.13 (IN), U13.14 (IN), U16.6 (OUT_S), U16.9 (OUT), U16.10 (OUT)
VIN_5V: C206.1, C207.1, C209.1, J3.19 (5V_IN), TP14.1 (PAD_1), U16.3 (EN), U16.12 (IN), U16.13 (IN), U16.14 (IN)
